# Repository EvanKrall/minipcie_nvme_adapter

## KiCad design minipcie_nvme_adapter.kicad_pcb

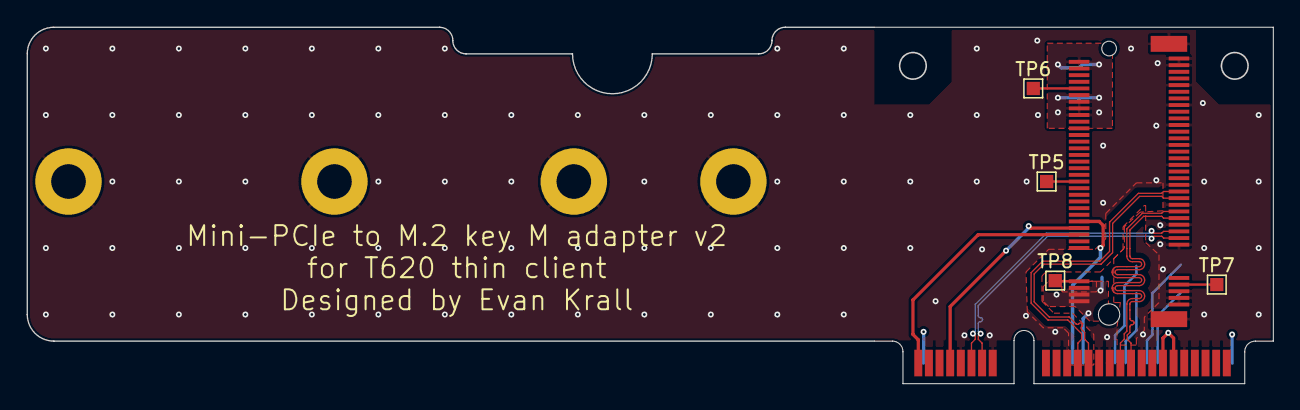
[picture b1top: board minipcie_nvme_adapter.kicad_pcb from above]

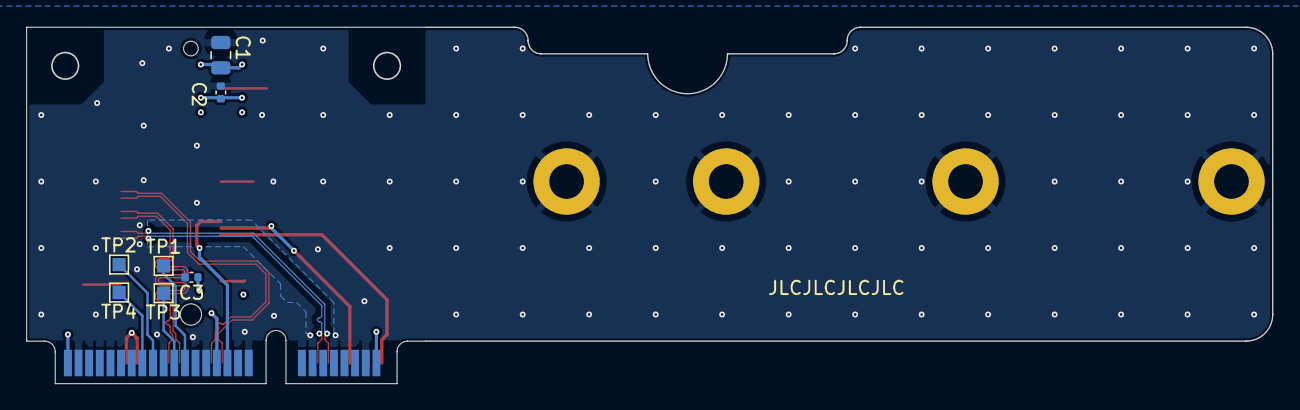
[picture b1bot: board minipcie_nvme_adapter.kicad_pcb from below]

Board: 4 copper layers, 93.6 x 26.7 mm, 13 parts (7 on the bottom side), 19 nets.

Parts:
C1: C; C_0805_2012Metric
C2, C3: C; C_0402_1005Metric
J1: Bus_PCI_Express_Mini; mpcie-half-card
J2: Bus_M.2_Socket_M; 246411067101894M_and_SM3ZS067U215-NUT1
TP1, TP2, TP3, TP4, TP5, TP6, TP7, TP8: TestPoint; TestPoint_Pad_1.0x1.0mm

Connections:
/3.3V: C1.1, C2.1, C3.1, J1.2 (+3V3AUX), J1.24 (+3V3AUX), J1.39 (+3V3AUX), J1.41 (+3V3AUX), J1.52 (+3V3AUX), J2.2 (3.3V), J2.4 (3.3V), J2.12 (3.3V), J2.14 (3.3V), J2.16 (3.3V), J2.18 (3.3V), J2.70 (3.3V), J2.72 (3.3V), J2.74 (3.3V)
/PER_0+: J1.25 (PERp0), J2.43 (PERp0/SATA-B-)
/PER_0-: J1.23 (PERn0), J2.41 (PERn0/SATA-B+)
/PET_0+: J1.33 (PETp0), J2.49 (PETp0/SATA-A+)
/PET_0-: J1.31 (PETn0), J2.47 (PETn0/SATA-A-)
/REFCLK+: J1.13 (REFCLK+), J2.55 (REFCLKp)
/REFCLK-: J1.11 (REFCLK-), J2.53 (REFCLKn)
/~CLKREQ: J1.7 (~CLKREQ), J2.52 (~CLKREQ)
/~PERST: J1.22 (~PERST), J2.50 (~PERST)
/~PEWAKE: J1.1 (~WAKE), J2.54 (~PEWAKE)
GND: C1.2, C2.2, C3.2, J1.4 (GND), J1.9 (GND), J1.15 (GND), J1.18 (GND), J1.21 (GND), J1.26 (GND), J1.27 (GND), J1.29 (GND), J1.34 (GND), J1.35 (GND), J1.37 (GND), J1.40 (GND), J1.43 (GND), J1.50 (GND), J2.0 (MP), J2.1 (GND), J2.3 (GND), J2.9 (GND), J2.15 (GND), J2.21 (GND), J2.27 (GND), J2.33 (GND), J2.39 (GND), J2.45 (GND), J2.51 (GND), J2.57 (GND), J2.71 (GND), J2.73 (GND), J2.75 (GND)
unnamed: J1.30 (SMB_CLK), TP1.1
unnamed: J1.32 (SMB_DATA), TP3.1
unnamed: J1.36 (USB_D-), TP2.1
unnamed: J1.38 (USB_D+), TP4.1
unnamed: J2.10 (DAS/~DSS/~LED1), TP6.1
unnamed: J2.38 (DEVSLP), TP5.1
unnamed: J2.68 (SUSCLK), TP8.1
unnamed: J2.69 (PEDET), TP7.1

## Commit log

2022-06-07 Move m.2 connector right so that we can fit up to 2280 cards without exceeding 100mm width
2022-06-07 Pull planes on inner layers away from edge of mini-pcie connector so they don't get exposed when chamfering the edge.
2022-06-25 Fix minimum track width, re-route differential pairs, and shrink the size of the holes so that the head of my M1.6 screws don't fit through the gap.
    Also inline the mpcie-half-card.kicad_mod file into this project instead of using submodules.
2022-06-26 Add a little cutout to avoid physical conflict with the existing 2242 SSD.
